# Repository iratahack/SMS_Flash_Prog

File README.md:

# SEGA Master System Flash Cartridge Programmer

A small USB/Arduino-based programmer and diagnostic tool for Sega Master System ROM cartridges.
It provides a serial-menu interface to identify the cartridge flash, erase and program NOR flash chips,
read or write individual bytes, perform blank checks, and transfer full ROM images using XMODEM-1K.
This repository contains the firmware source (AVR C) used on the programmer hardware and example
host-side workflows for sending/receiving ROM images.

## Hardware

The programmer is an ATmega328p (Arduino Uno / Nano) running at 16 MHz. It accesses the SMS
cartridge slot through the following bus signals:

- **Address bus (A0–A15)**: driven by two cascaded 74HC595 shift registers clocked over the ATmega's SPI peripheral (MOSI=PB3, SCK=PB5, SS=PB2). A high pulse on **RCLK** (PC0) latches the shifted address onto the cartridge bus.
- **Data bus (D0–D7)**: bidirectional GPIO on Arduino pins D2–D9 (PD2–PD7 and PB0–PB1). Direction is toggled per read/write.
- **Control signals**: `_CE` on PC1, `_RD` on PC2, `_WR` on PC3, `_RST` on PC4 (all active low).

KiCad design files for the programmer shield — including schematic, PCB, and Gerbers — live in
[`Arduino_SMS_Cart_Programmer/`](Arduino_SMS_Cart_Programmer/).

### Supported flash chips & Carts

The firmware auto-detects the flash device using the AMD/SST JEDEC ID command sequence and
currently recognises the SST39SF family:

| Manufacturer ID | Device ID | Part       | Size  |
| --------------- | --------- | ---------- | ----- |
| `0xBF` (SST)    | `0xB5`    | SST39SF010 | 128 KB |
| `0xBF` (SST)    | `0xB6`    | SST39SF020 | 256 KB |
| `0xBF` (SST)    | `0xB7`    | SST39SF040 | 512 KB |

The programmer has been tested with the flash cart by [ichigobankai](https://github.com/ichigobankai/SMS_PCB_SLOT1-2_2GAL_DIP)

### Supported mappers

The firmware auto-detects the cartridge mapper at boot and can be switched manually from the menu:

- **SEGA** — standard 16 KB-banked SEGA mapper (bank register at `0xFFFF`).
- **Iratahack** — 3-bit bank + 2-bit game slot (`0xFFFE` / `0xFFFF`) for multi-game carts.

## Building the firmware

Install the AVR toolchain:

```sh
sudo apt-get install gcc-avr avr-libc avrdude
```

Build from the `src/` directory:

```sh
cd src
make                    # compile -> SMSFlasher.bin
make SMSFlasher.bin.hex # Intel HEX output (flashable with avrdude)
make clean              # remove build artifacts
make dis                # disassembly via avr-objdump | less
```

A separate diagnostic firmware that exercises just the 74HC595 address-bus shift registers
lives in [`74hc595/`](74hc595/) and builds with its own `Makefile` in the same way.

Pre-built releases are published on the GitHub Releases page when a `release/vX.Y.Z` tag
is pushed; each release includes `SMSFlasher.bin` and `SMSFlasher.bin.hex`.

## Flashing the firmware to the Arduino

With the Arduino connected as `/dev/ttyUSB0`:

```sh
cd src
make download
```

This runs `avrdude -c arduino -p atmega328p -P /dev/ttyUSB0 -b 115200` against
`SMSFlasher.bin.hex`. Override the port/programmer by editing the `download` target
if your setup differs.

### Arduino COM port setup for WSL

After connecting the programmer via USB to a Windows machine, enter the command below in an
administrator PowerShell to attach the Arduino COM port from Windows to WSL:

```sh
usbipd list # look for USB-SERIAL CH340 (COM4) or similar
usbipd bind --busid <BUSIS> # as administrator
usbipd attach --wsl --busid <BUSID>
```

If the error below is displayed and you already have the latest install of WSL try
`sudo modprobe vhci_hcd` from WSL:

```
usbipd: info: Using WSL distribution 'Ubuntu-22.04' to attach; the device will be available in all WSL 2 distributions.
usbipd: error: WSL kernel is not USBIP capable; update with 'wsl --update'.
```

## Using the programmer

Remember to disconnect the USB connector (power) before connecting or disconnecting a Sega Master System cartridge to
avoid damaging the cartridge or the programmer. When connecting the cartridge, insert the cartridge into the connector
with the front of the cartridge facing the Arduino.

Once the firmware is running, connect a serial terminal to the device at **1,000,000 baud**,
8-N-1, no flow control. The UI uses ANSI colour and Unicode box-drawing characters, so
use a terminal that supports both (e.g. `picocom`, `minicom`). On Windows,
[ExtraPUTTY](https://sourceforge.net/projects/extraputty/) is a good choice and supports
XMODEM-1K for file transfer.

The firmware redraws a full-screen menu on each iteration:

| Key | Action |
| --- | ------ |
| `1` | Erase flash (full-chip erase) |
| `2` | Blank check — scan entire flash for `0xFF` |
| `3` | Program flash (receive ROM image over XMODEM-1K) |
| `4` | Checksum — compute CRC32 of flash and compare against last programmed CRC32 |
| `5` | Read a single byte from a hex address |
| `6` | Program a single byte at a hex address |
| `7` | Read ROM — send full flash contents to host over XMODEM-1K |
| `8` | Display SDSC ROM header (if present) |
| `9` | Erase, program (XMODEM-1K), and verify in one step |
| `0` | Toggle between detected mappers (SEGA / Iratahack) |
| `s` | Change ROM/flash size |

The flash size used by operations `2`, `4`, `7`, and `9` is determined by the JEDEC ID
read at each menu redraw, so the programmer adapts automatically to whichever SST39SF
part is installed.

### Transferring ROM images over XMODEM

The firmware uses **XMODEM-1K** (1024-byte packets with CRC-16). The receive path also
accepts classic 128-byte XMODEM packets, but the send path always transmits 1K blocks.
ExtraPUTTY includes XMODEM-1K support for both sending and receiving.

## Repository layout

- [`src/`](src/) — programmer firmware (main target).
- [`74hc595/`](74hc595/) — standalone test firmware that cycles the address-bus shift registers.
- [`Arduino_SMS_Cart_Programmer/`](Arduino_SMS_Cart_Programmer/) — KiCad hardware design files.
- [`.github/workflows/build.yml`](.github/workflows/build.yml) — CI build and release workflow.

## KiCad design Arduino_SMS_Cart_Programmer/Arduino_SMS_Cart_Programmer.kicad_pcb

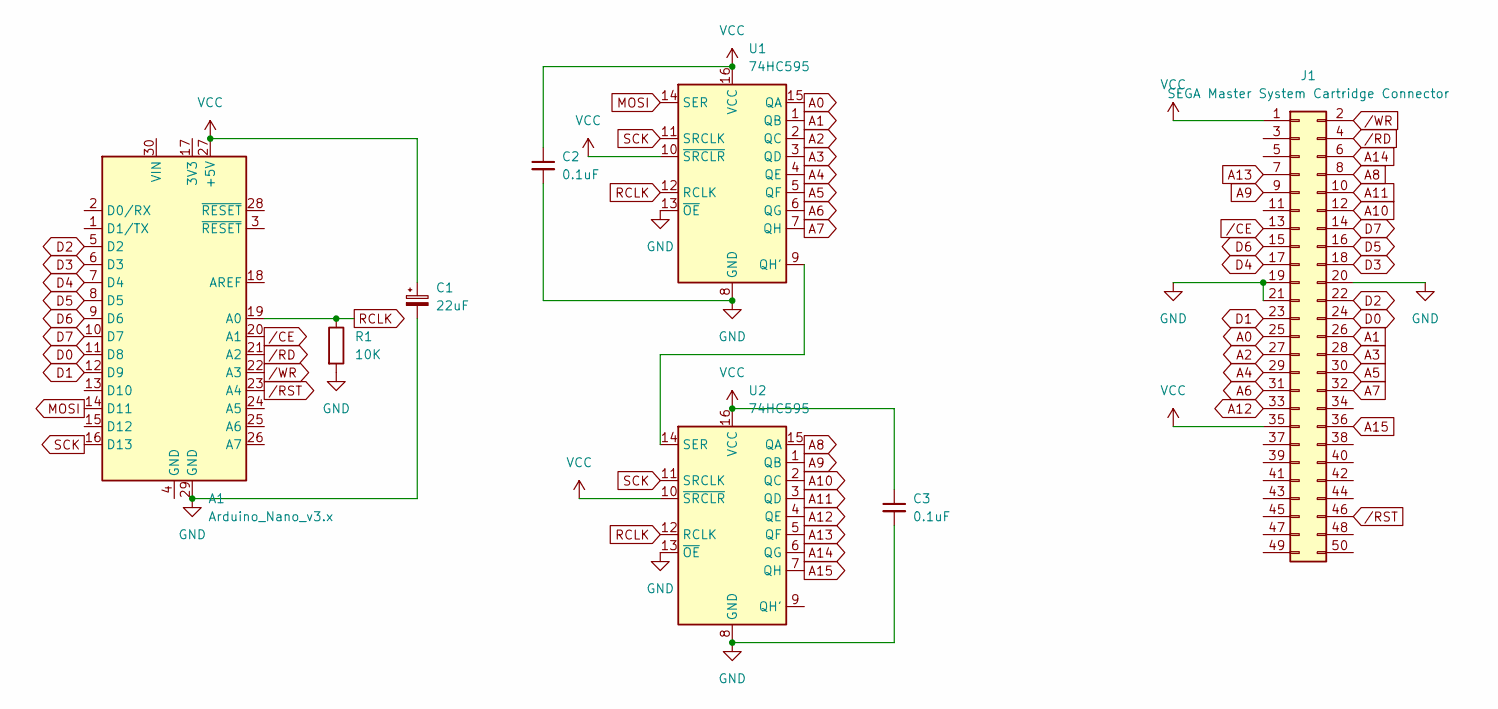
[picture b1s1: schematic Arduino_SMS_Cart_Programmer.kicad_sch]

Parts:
A1: Arduino_Nano_v3.x; Arduino_Nano
C1: 22uF; CP_Radial_D5.0mm_P2.00mm
C2, C3: 0.1uF; C_Disc_D4.3mm_W1.9mm_P5.00mm
J1: SEGA Master System Cartridge Connector; SEGA_Master_System_Cart_Connector
R1: 10K; R_Axial_DIN0204_L3.6mm_D1.6mm_P7.62mm_Horizontal
U1, U2: 74HC595; DIP-16_W7.62mm

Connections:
A0: J1.25, U1.15 (QA)
A1: J1.26, U1.1 (QB)
A2: J1.27, U1.2 (QC)
A3: J1.28, U1.3 (QD)
A4: J1.29, U1.4 (QE)
A5: J1.30, U1.5 (QF)
A6: J1.31, U1.6 (QG)
A7: J1.32, U1.7 (QH)
A8: J1.8, U2.15 (QA)
A9: J1.9, U2.1 (QB)
A10: J1.12, U2.2 (QC)
A11: J1.10, U2.3 (QD)
A12: J1.33, U2.4 (QE)
A13: J1.7, U2.5 (QF)
A14: J1.6, U2.6 (QG)
A15: J1.36, U2.7 (QH)
D0: A1.11 (D8), J1.24
D1: A1.12 (D9), J1.23
D2: A1.5 (D2), J1.22
D3: A1.6 (D3), J1.18
D4: A1.7 (D4), J1.17
D5: A1.8 (D5), J1.16
D6: A1.9 (D6), J1.15
D7: A1.10 (D7), J1.14
GND: A1.29 (GND), C1.2, C2.2, C3.2, J1.19, J1.20, J1.21, R1.2, U1.8 (GND), U1.13 (~OE), U2.8 (GND), U2.13 (~OE)
MOSI: A1.14 (D11), U1.14 (SER)
unnamed: U1.9 (QH'), U2.14 (SER)
RCLK: A1.19 (A0), R1.1, U1.12 (RCLK), U2.12 (RCLK)
SCK: A1.16 (D13), U1.11 (SRCLK), U2.11 (SRCLK)
VCC: A1.27 (+5V), C1.1, C2.1, C3.1, J1.1, J1.35, U1.10 (~SRCLR), U1.16 (VCC), U2.10 (~SRCLR), U2.16 (VCC)
/CE: A1.20 (A1), J1.13
/RD: A1.21 (A2), J1.4
/RST: A1.23 (A4), J1.46
/WR: A1.22 (A3), J1.2

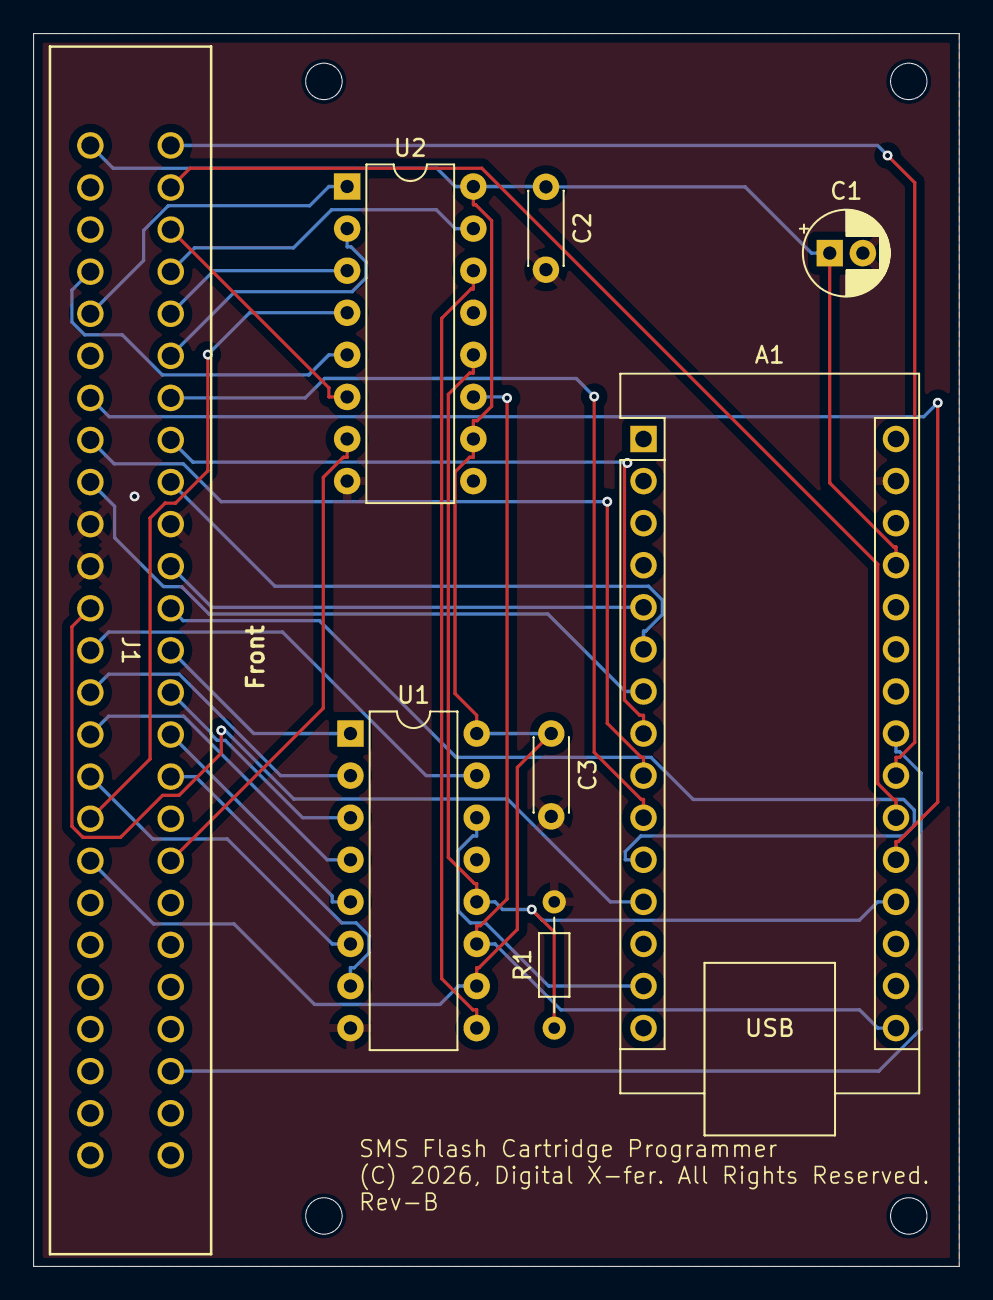
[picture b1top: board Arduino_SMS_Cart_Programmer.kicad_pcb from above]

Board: 2 copper layers, 55.9 x 74.4 mm, 12 parts (0 on the bottom side), 34 nets.

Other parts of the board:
REF1, REF2, REF3, REF4: MountingHole_2.2mm_M2

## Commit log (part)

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2025-10-21 Initial checkin.
2025-10-22 Add CRC32 calculation and XMODEM protocol enhancements
    - Implemented CRC32 table and update function in CRC32.c.
    - Enhanced main.c with flash programming features and improved user interface.
    - Modified timer.c for better tick management.
    - Adjusted UART baud rate in uart.c for higher speed.
    - Refined xmodem.c for improved data handling and error checking.
2025-10-23 Added support for XMODEM-1K
2025-10-23 Moved const strings from printf to flash memory.
2025-10-24 Added read/write byte to flash.
2025-11-02 Initial tested version.
2025-11-02 Added dummy read to allow data to stabilize.
2025-11-02 Minor cleanup.
2025-11-04 Added upload of cart data using Iratahack multi-game mapper.
2025-11-05 Code cleanup.
2025-11-05 Highlight checksum pass/fail text.
2025-11-05 Update README.md to enhance documentation on Arduino COM port setup and menu options
2025-11-06 Speed up crc16 algorithm by using a lookup table in flash mem.
2025-11-06 Speed optimizations by only updating slot and bank when needed.
2025-11-06 Code optimizations.
2025-11-07 Enhance ROM header display functionality and improve data stabilization during read operations
2025-11-14 Improve ROM header signature verification before display
2025-11-27 Add ANSI color support and improve UI display functions for better user experience
2025-11-27 Enhance error and status messages with ANSI color coding for improved visibility
2025-12-04 SPI test program for 74hc595 shift register.
2025-12-11 Updated cart programmer to support multiple mappers.
2025-12-12 Add raw cart byte reading and mapper detection functionality.
2025-12-12 Set mapperIndex to that of detected mapper.
2025-12-12 Flush remaining characters in XMODEM_ReceiveFile to ensure clean input before processing
2025-12-12 Update XMODEM program prompts to specify 1K transfer mode
2025-12-12 Refactor UI functions to remove unused animation parameters
2026-02-28 Refactor: improve documentation, code quality, and add CI/CD pipeline
    Changes:
    - Create GitHub Copilot workspace instructions
    - Simplify README with hardware interface details
    - Fix critical issue: buffer type int8_t -> uint8_t
    - Optimize RAM: box drawing in PROGMEM via defines
    - Rename mapper: Multi-game -> Iratahack
2026-02-28 Fix build process to compile all targets instead of just SMSFlasher.hex
2026-02-28 Add missing include for stdbool in mappers.h
2026-02-28 Remove SMSFlasher.hex from release artifacts in build workflow
2026-02-28 Update build workflow to compile specific target and include HEX file in release
2026-02-28 Fix: Add write permissions to GitHub Actions workflow for release creation
2026-03-02 Fix WSL setup typos
2026-05-11 Update README.md to enhance hardware setup instructions and add firmware building details
2026-05-12 Lowered baud to 1,000,000.
2026-05-12 Update README.md to clarify supported flash chips and improve usage instructions

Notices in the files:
Arduino_SMS_Cart_Programmer/Arduino_SMS_Cart_Programmer.kicad_pcb:
(C) 2026, Digital X-fer. All Rights Reserved.
